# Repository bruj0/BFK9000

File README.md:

# BFK9000
Building it

Finished look

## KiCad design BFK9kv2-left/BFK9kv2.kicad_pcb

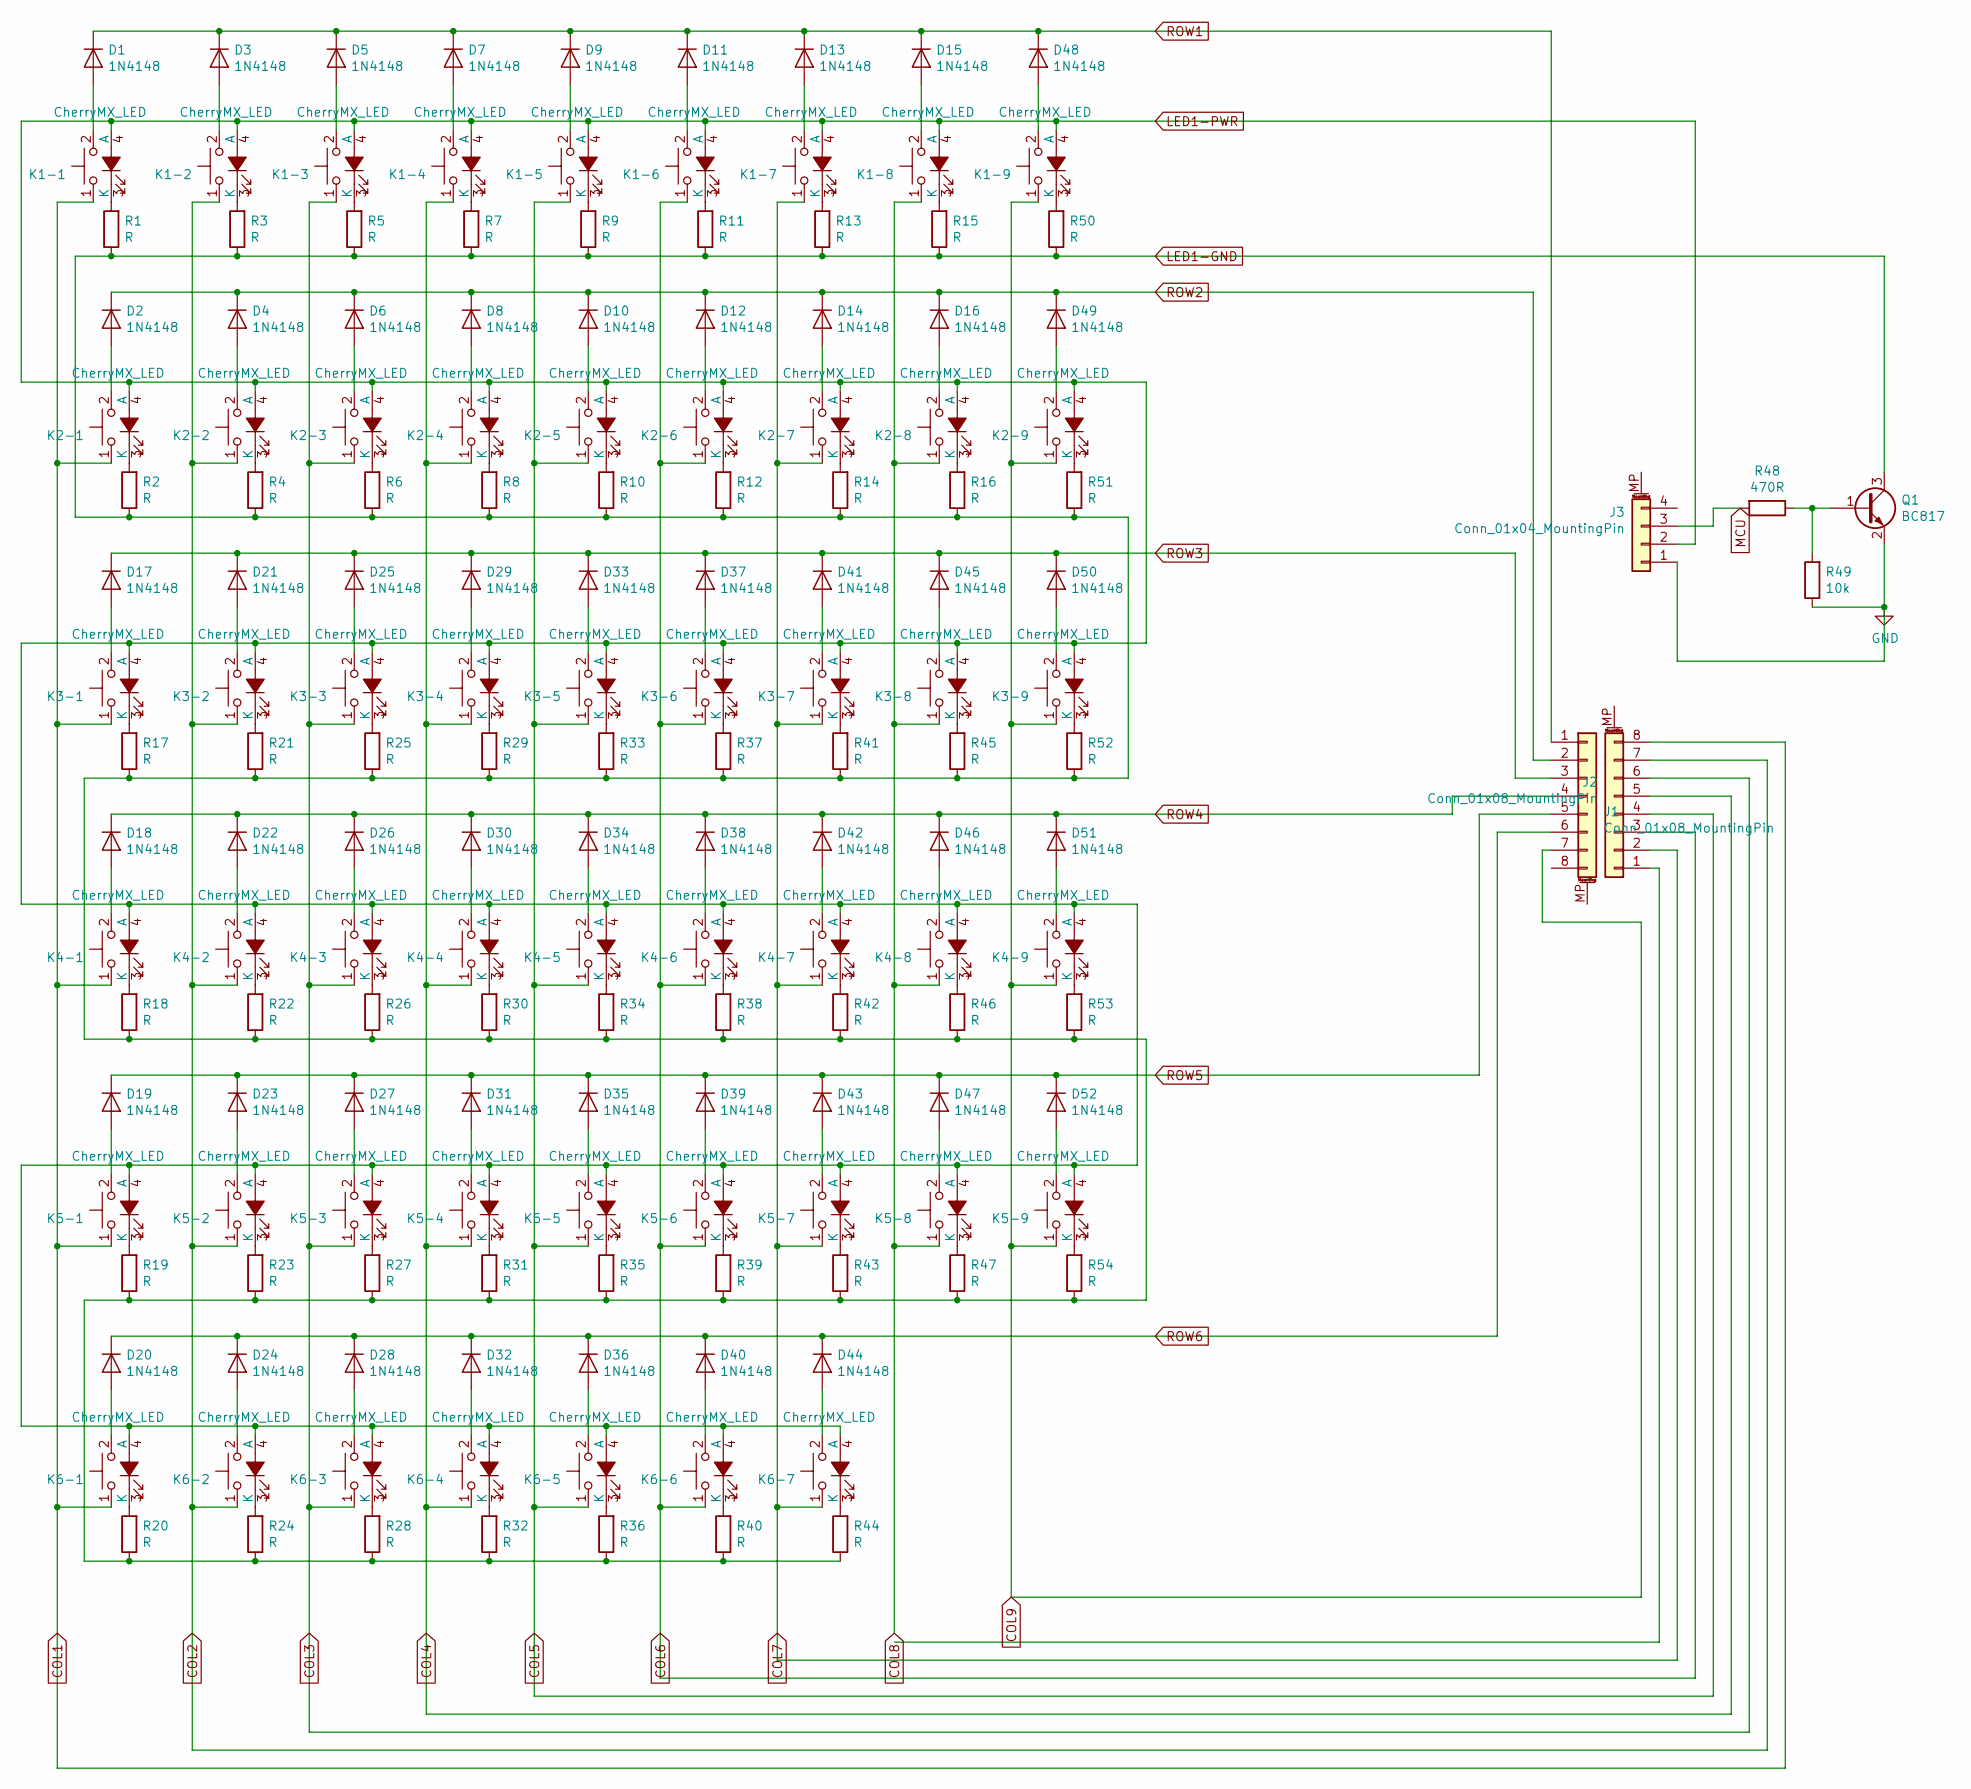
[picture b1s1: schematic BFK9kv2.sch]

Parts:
D1, D2, D3, D4, D5, D6, D7, D8, D9, D10, D11, D12, D13, D14, D15, D16, D17, D18, D19, D20, D21, D22, D23, D24, D25, D26, D27, D28, D29, D30, D31, D32, D33, D34, D35, D36, D37, D38, D39, D40, D41, D42, D43, D44, D45, D46, D47, D48, D49, D50, D51, D52: 1N4148; D_DO-35_SOD27_P7.62mm_Horizontal
J1, J2: Conn_01x08_MountingPin; PinHeader_1x08_P2.00mm_Vertical
J3: Conn_01x04_MountingPin; PinHeader_1x04_P2.00mm_Vertical
K1-1, K1-2, K1-3, K1-5, K1-6, K1-7, K1-8, K1-9, K2-1, K2-2, K2-3, K2-5, K2-6, K2-7, K2-8, K2-9, K3-1, K3-2, K3-3, K3-5, K3-6, K3-7, K3-8, K3-9, K4-1, K4-2, K4-3, K4-5, K4-6, K4-7, K4-8, K4-9, K5-1, K5-2, K5-3, K5-5, K5-6, K5-7, K5-8, K5-9, K6-1, K6-2, K6-3: CherryMX_LED; CherryMX_1.00u_PCB_LED
K1-4, K2-4, K3-4, K4-4, K5-4, K6-4, K6-5, K6-6: CherryMX_LED; CherryMX_1.50u_PCB_LED
K6-7: CherryMX_LED; CherryMX_2.00u_PCB_LED
Q1: BC817; SOT-23
R1, R2, R3, R4, R5, R6, R7, R8, R9, R10, R11, R12, R13, R14, R15, R16, R17, R18, R19, R20, R21, R22, R23, R24, R25, R26, R27, R28, R29, R30, R31, R32, R33, R34, R35, R36, R37, R38, R39, R40, R41, R42, R43, R44, R45, R46, R47, R50, R51, R52, R53, R54: R; R_Axial_DIN0207_L6.3mm_D2.5mm_P15.24mm_Horizontal
R48: 470R; R_0805_2012Metric_Pad1.15x1.40mm_HandSolder
R49: 10k; R_0805_2012Metric_Pad1.15x1.40mm_HandSolder

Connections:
COL1: J2.8, K1-1.1, K2-1.1, K3-1.1, K4-1.1, K5-1.1, K6-1.1
COL2: J2.7, K1-2.1, K2-2.1, K3-2.1, K4-2.1, K5-2.1, K6-2.1
COL3: J2.6, K1-3.1, K2-3.1, K3-3.1, K4-3.1, K5-3.1, K6-3.1
COL4: J2.5, K1-4.1, K2-4.1, K3-4.1, K4-4.1, K5-4.1, K6-4.1
COL5: J2.4, K1-5.1, K2-5.1, K3-5.1, K4-5.1, K5-5.1, K6-5.1
COL6: J2.3, K1-6.1, K2-6.1, K3-6.1, K4-6.1, K5-6.1, K6-6.1
COL7: J2.2, K1-7.1, K2-7.1, K3-7.1, K4-7.1, K5-7.1, K6-7.1
COL8: K1-8.1, K2-8.1, K3-8.1, K4-8.1, K5-8.1
COL9: J1.7, K1-9.1, K2-9.1, K3-9.1, K4-9.1, K5-9.1
GND: J3.1, Q1.2 (E), R49.1
LED1-GND: Q1.3 (C), R1.1, R2.1, R3.1, R4.1, R5.1, R6.1, R7.1, R8.1, R9.1, R10.1, R11.1, R12.1, R13.1, R14.1, R15.1, R16.1, R17.1, R18.1, R19.1, R20.1, R21.1, R22.1, R23.1, R24.1, R25.1, R26.1, R27.1, R28.1, R29.1, R30.1, R31.1, R32.1, R33.1, R34.1, R35.1, R36.1, R37.1, R38.1, R39.1, R40.1, R41.1, R42.1, R43.1, R44.1, R45.1, R46.1, R47.1, R50.1, R51.1, R52.1, R53.1, R54.1
LED1-PWR: J3.2, K1-1.4 (A), K1-2.4 (A), K1-3.4 (A), K1-4.4 (A), K1-5.4 (A), K1-6.4 (A), K1-7.4 (A), K1-8.4 (A), K1-9.4 (A), K2-1.4 (A), K2-2.4 (A), K2-3.4 (A), K2-4.4 (A), K2-5.4 (A), K2-6.4 (A), K2-7.4 (A), K2-8.4 (A), K2-9.4 (A), K3-1.4 (A), K3-2.4 (A), K3-3.4 (A), K3-4.4 (A), K3-5.4 (A), K3-6.4 (A), K3-7.4 (A), K3-8.4 (A), K3-9.4 (A), K4-1.4 (A), K4-2.4 (A), K4-3.4 (A), K4-4.4 (A), K4-5.4 (A), K4-6.4 (A), K4-7.4 (A), K4-8.4 (A), K4-9.4 (A), K5-1.4 (A), K5-2.4 (A), K5-3.4 (A), K5-4.4 (A), K5-5.4 (A), K5-6.4 (A), K5-7.4 (A), K5-8.4 (A), K5-9.4 (A), K6-1.4 (A), K6-2.4 (A), K6-3.4 (A), K6-4.4 (A), K6-5.4 (A), K6-6.4 (A), K6-7.4 (A)
MCU: J3.3, R48.2
unnamed: D1.2 (A), K1-1.2
unnamed: D2.2 (A), K2-1.2
unnamed: D3.2 (A), K1-2.2
unnamed: D4.2 (A), K2-2.2
unnamed: D5.2 (A), K1-3.2
unnamed: D6.2 (A), K2-3.2
unnamed: D7.2 (A), K1-4.2
unnamed: D8.2 (A), K2-4.2
unnamed: D9.2 (A), K1-5.2
unnamed: D10.2 (A), K2-5.2
unnamed: D11.2 (A), K1-6.2
unnamed: D12.2 (A), K2-6.2
unnamed: D13.2 (A), K1-7.2
unnamed: D14.2 (A), K2-7.2
unnamed: D15.2 (A), K1-8.2
unnamed: D16.2 (A), K2-8.2
unnamed: D17.2 (A), K3-1.2
unnamed: D18.2 (A), K4-1.2
unnamed: D19.2 (A), K5-1.2
unnamed: D20.2 (A), K6-1.2
unnamed: D21.2 (A), K3-2.2
unnamed: D22.2 (A), K4-2.2
unnamed: D23.2 (A), K5-2.2
unnamed: D24.2 (A), K6-2.2
unnamed: D25.2 (A), K3-3.2
unnamed: D26.2 (A), K4-3.2
unnamed: D27.2 (A), K5-3.2
unnamed: D28.2 (A), K6-3.2
unnamed: D29.2 (A), K3-4.2
unnamed: D30.2 (A), K4-4.2
unnamed: D31.2 (A), K5-4.2
unnamed: D32.2 (A), K6-4.2
unnamed: D33.2 (A), K3-5.2
unnamed: D34.2 (A), K4-5.2
unnamed: D35.2 (A), K5-5.2
unnamed: D36.2 (A), K6-5.2
unnamed: D37.2 (A), K3-6.2
unnamed: D38.2 (A), K4-6.2
unnamed: D39.2 (A), K5-6.2
unnamed: D40.2 (A), K6-6.2
unnamed: D41.2 (A), K3-7.2
unnamed: D42.2 (A), K4-7.2
unnamed: D43.2 (A), K5-7.2
unnamed: D44.2 (A), K6-7.2
unnamed: D45.2 (A), K3-8.2
unnamed: D46.2 (A), K4-8.2
unnamed: D47.2 (A), K5-8.2
unnamed: D48.2 (A), K1-9.2
unnamed: D49.2 (A), K2-9.2
unnamed: D50.2 (A), K3-9.2
unnamed: D51.2 (A), K4-9.2
unnamed: D52.2 (A), K5-9.2
unnamed: K1-1.3 (K), R1.2
unnamed: K1-2.3 (K), R3.2
unnamed: K1-3.3 (K), R5.2
unnamed: K1-4.3 (K), R7.2
unnamed: K1-5.3 (K), R9.2
unnamed: K1-6.3 (K), R11.2
unnamed: K1-7.3 (K), R13.2
unnamed: K1-8.3 (K), R15.2
unnamed: K1-9.3 (K), R50.2
unnamed: K2-1.3 (K), R2.2
unnamed: K2-2.3 (K), R4.2
unnamed: K2-3.3 (K), R6.2
unnamed: K2-4.3 (K), R8.2
unnamed: K2-5.3 (K), R10.2
unnamed: K2-6.3 (K), R12.2
unnamed: K2-7.3 (K), R14.2
unnamed: K2-8.3 (K), R16.2
unnamed: K2-9.3 (K), R51.2
unnamed: K3-1.3 (K), R17.2
unnamed: K3-2.3 (K), R21.2
unnamed: K3-3.3 (K), R25.2
unnamed: K3-4.3 (K), R29.2
unnamed: K3-5.3 (K), R33.2
unnamed: K3-6.3 (K), R37.2
unnamed: K3-7.3 (K), R41.2
unnamed: K3-8.3 (K), R45.2
unnamed: K3-9.3 (K), R52.2
unnamed: K4-1.3 (K), R18.2
unnamed: K4-2.3 (K), R22.2
unnamed: K4-3.3 (K), R26.2
unnamed: K4-4.3 (K), R30.2
unnamed: K4-5.3 (K), R34.2
unnamed: K4-6.3 (K), R38.2
unnamed: K4-7.3 (K), R42.2
unnamed: K4-8.3 (K), R46.2
unnamed: K4-9.3 (K), R53.2
unnamed: K5-1.3 (K), R19.2
unnamed: K5-2.3 (K), R23.2
unnamed: K5-3.3 (K), R27.2
unnamed: K5-4.3 (K), R31.2
unnamed: K5-5.3 (K), R35.2
unnamed: K5-6.3 (K), R39.2
unnamed: K5-7.3 (K), R43.2
unnamed: K5-8.3 (K), R47.2
unnamed: K5-9.3 (K), R54.2
unnamed: K6-1.3 (K), R20.2
unnamed: K6-2.3 (K), R24.2
unnamed: K6-3.3 (K), R28.2
unnamed: K6-4.3 (K), R32.2
unnamed: K6-5.3 (K), R36.2
unnamed: K6-6.3 (K), R40.2
unnamed: K6-7.3 (K), R44.2
unnamed: Q1.1 (B), R48.1, R49.2
ROW1: D1.1 (K), D3.1 (K), D5.1 (K), D7.1 (K), D9.1 (K), D11.1 (K), D13.1 (K), D15.1 (K), D48.1 (K), J1.1
ROW2: D2.1 (K), D4.1 (K), D6.1 (K), D8.1 (K), D10.1 (K), D12.1 (K), D14.1 (K), D16.1 (K), D49.1 (K), J1.2
ROW3: D17.1 (K), D21.1 (K), D25.1 (K), D29.1 (K), D33.1 (K), D37.1 (K), D41.1 (K), D45.1 (K), D50.1 (K), J1.3
ROW4: D18.1 (K), D22.1 (K), D26.1 (K), D30.1 (K), D34.1 (K), D38.1 (K), D42.1 (K), D46.1 (K), D51.1 (K), J1.4
ROW5: D19.1 (K), D23.1 (K), D27.1 (K), D31.1 (K), D35.1 (K), D39.1 (K), D43.1 (K), D47.1 (K), D52.1 (K), J1.5
ROW6: D20.1 (K), D24.1 (K), D28.1 (K), D32.1 (K), D36.1 (K), D40.1 (K), D44.1 (K), J1.6

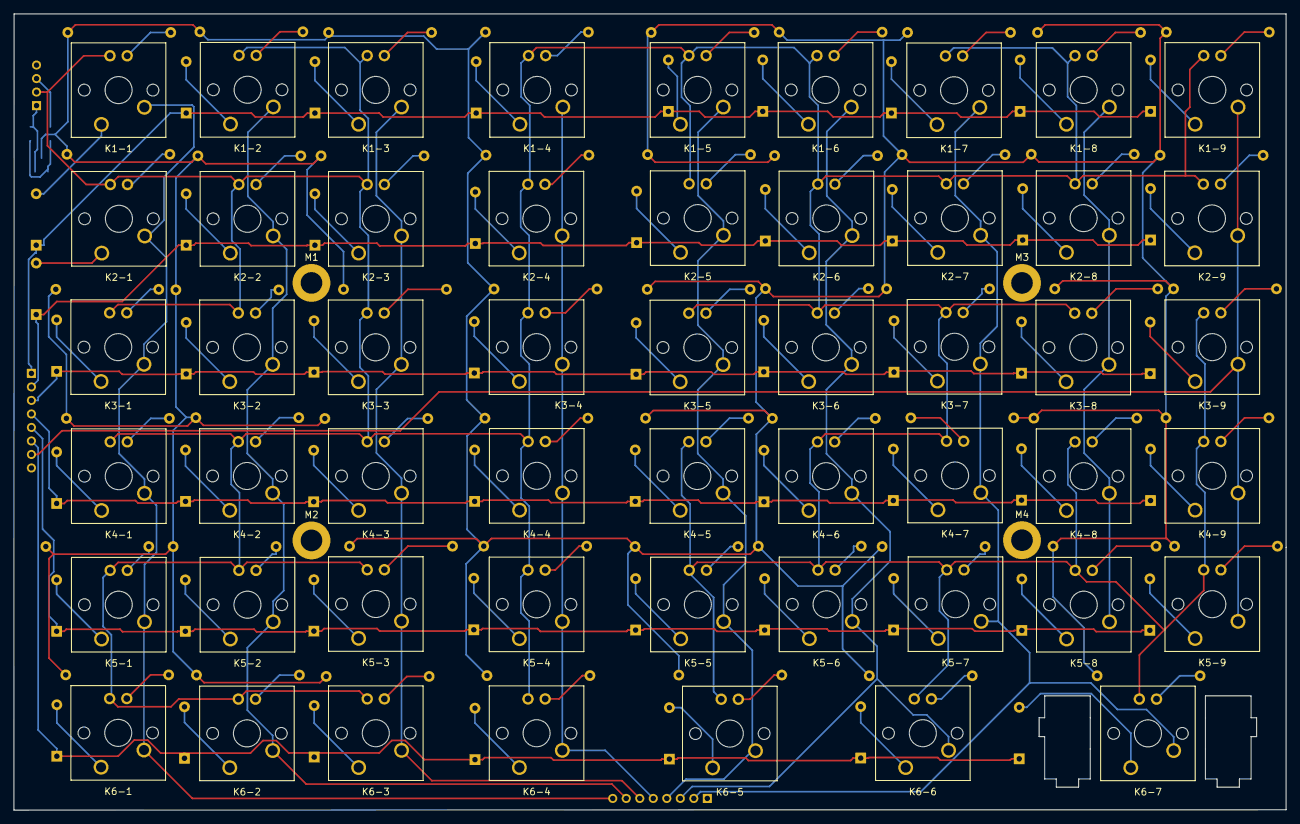
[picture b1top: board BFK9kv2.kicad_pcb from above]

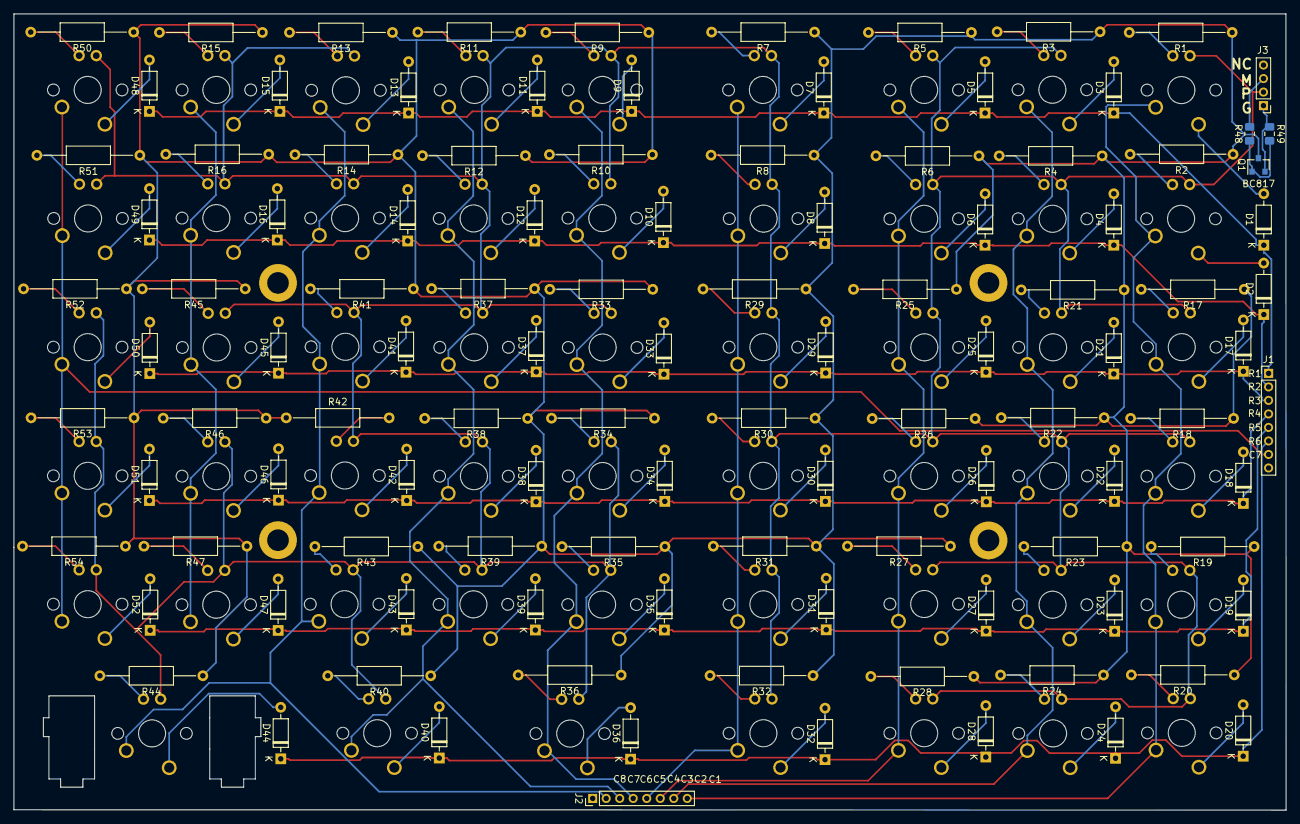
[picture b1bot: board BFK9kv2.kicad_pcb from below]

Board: 2 copper layers, 188.3 x 117.9 mm, 166 parts (110 on the bottom side), 124 nets.

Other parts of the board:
M1, M2, M3, M4: MountingHole_3.2mm_M3_DIN965_Pad

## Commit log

2021-09-16 First import
